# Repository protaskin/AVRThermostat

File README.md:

# AVRThermostat

AVRThermostat is, as the name implies, a programmable thermostat, which is built
on

* Atmel AVR ATmega8A microcontroller,

* digital thermometer DS18B20 by Maxim Integrated,

* four-digit seven-segment led display with common cathode (like CC56-12 or
FYQ-5641A),

and uses a relay to control a heater or fan. The device can be used as a simple
thermometer as well. The sensor measures temperatures from -55°C to +125°C
with ±0.5°C accuracy from -10°C to +85°C.

The thermostat has 4 buttons (Plus, Minus, Set, Reset) that are used to set up
parameters--the setpoint and the zone (delta). The longer you hold the 
Plus/Minus button, the faster a parameter increases/decreases. The Reset button
is used to set the standard value to a parameter, also to switch off the
thermostat mode. Parameters are saved in EEPROM after editing.

The Plus/Minus buttons also are used to adjust the display brightness when
the device is not in the mode of editing of a parameter.

Two leds indicate the state of the relay. If the device is not in the thermostat
mode, then both leds do not light.

If the device cannot establish connection with the sensor, the display shows
an error.

## Schematics and PCB Layout r3.x

A KiCad project, which includes a schematics and PCB layout, is located in
[the Design directory](Design/). **Please be aware that the project is made from
scratch and I have not yet used the new PCB layout myself, therefore it may have
errors.**

### Schematics

### PCB 3D Model

## Versioning

For transparency and insight into our release cycle, and for striving to
maintain backwards compatibility, AVRThermostat will be maintained under the
Semantic Versioning guidelines as much as possible.

For more information on SemVer, please visit http://semver.org/

## License

Copyright 2014-2017 Artyom Protaskin

Licensed under the MIT License:

http://opensource.org/licenses/MIT

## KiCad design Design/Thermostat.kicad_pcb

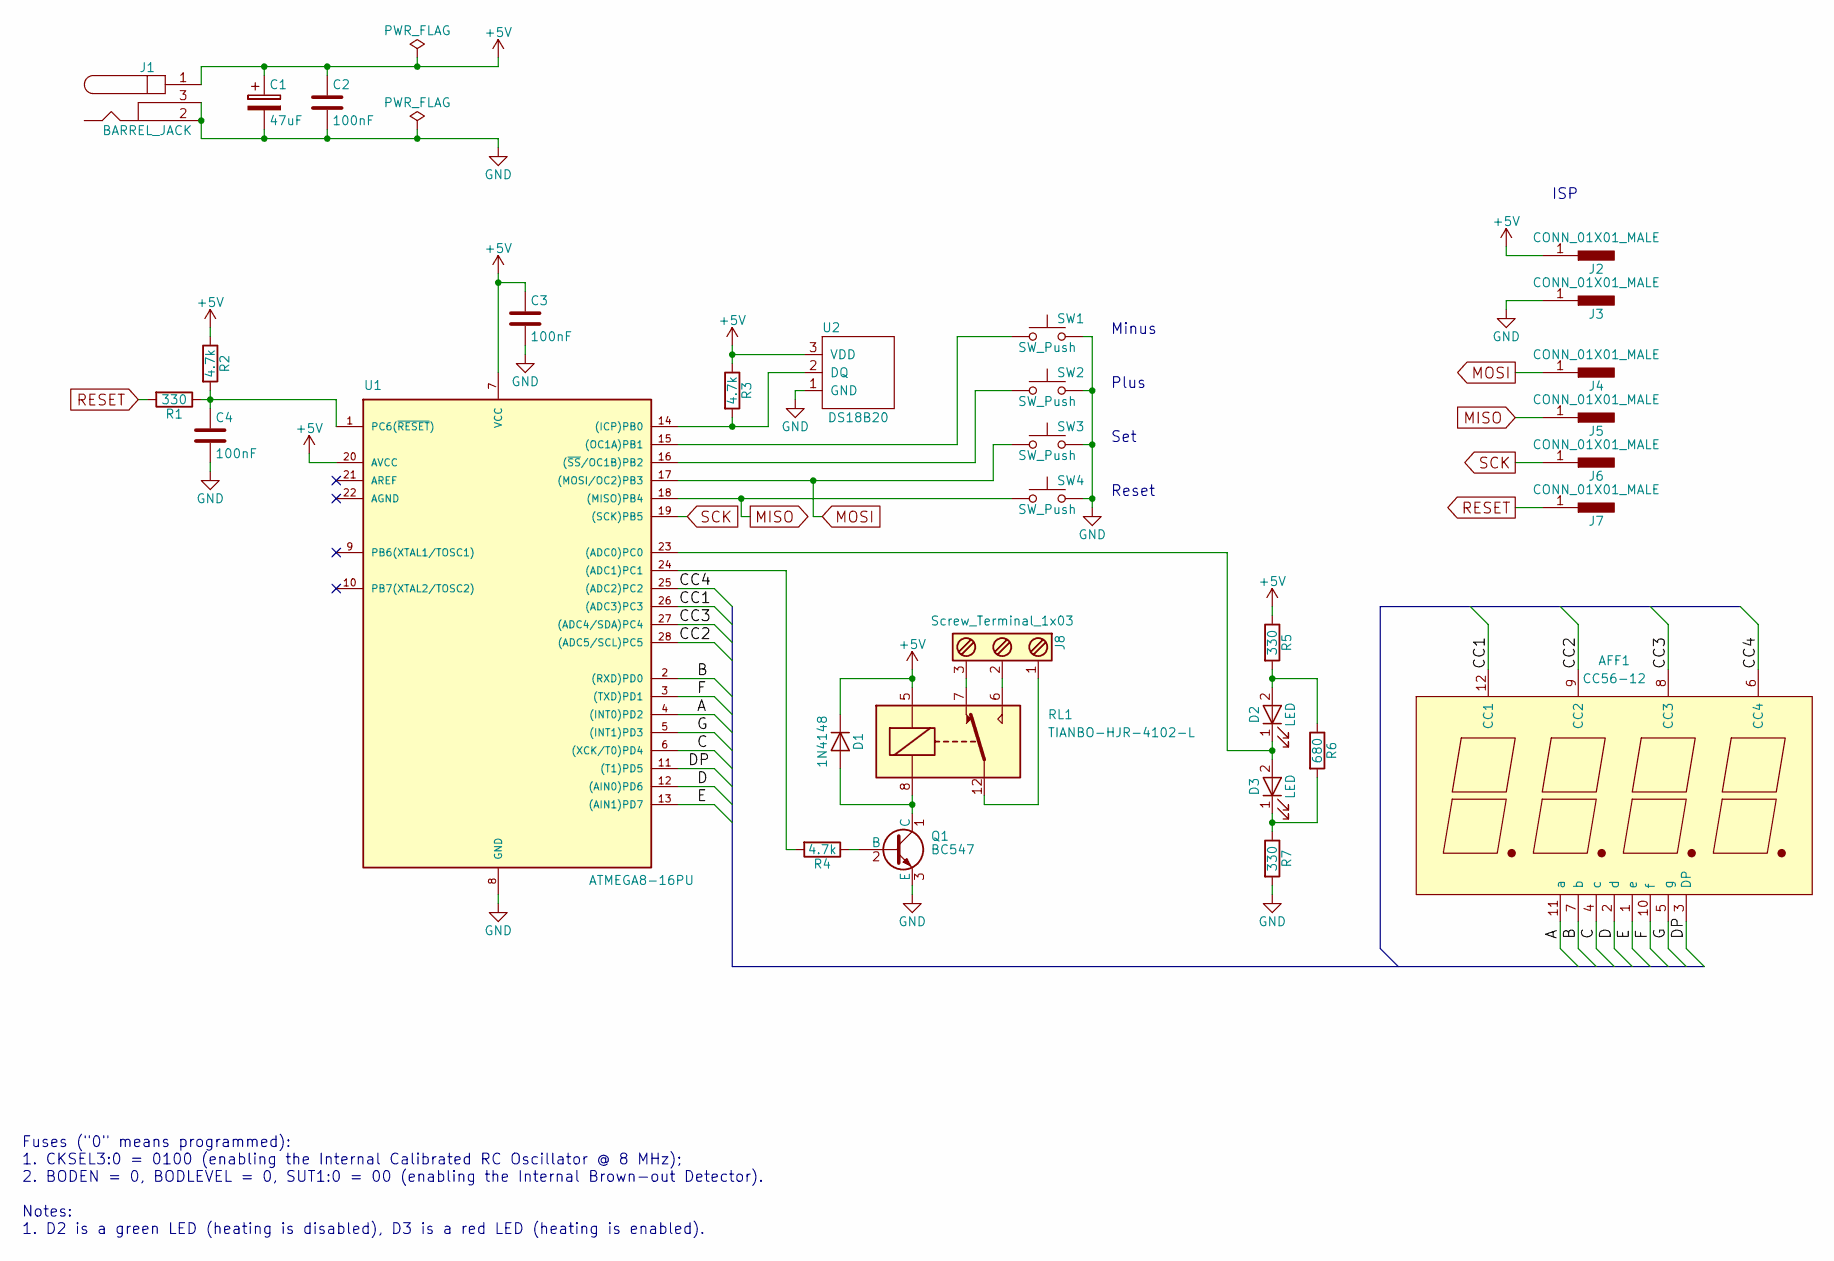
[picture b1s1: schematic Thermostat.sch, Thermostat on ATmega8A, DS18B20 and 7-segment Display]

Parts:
AFF1: CC56-12; CC56-12GWA
C1: 47uF; CP_Radial_D5.0mm_P2.00mm
C2, C3, C4: 100nF; C_Disc_D4.3mm_W1.9mm_P5.00mm
D1: 1N4148; D_DO-35_SOD27_P7.62mm_Horizontal
D2, D3: LED; LED_D3.0mm
J1: BARREL_JACK
J2, J3, J4, J5, J6, J7: CONN_01X01_MALE; Pin_Header_Straight_1x01_Pitch2.54mm
J8: Screw_Terminal_1x03; TerminalBlock_Pheonix_MKDS1.5-3pol
Q1: BC547; TO-92_Molded_Narrow
R1, R5, R7: 330; R_Axial_DIN0207_L6.3mm_D2.5mm_P10.16mm_Horizontal
R2, R3, R4: 4.7k; R_Axial_DIN0207_L6.3mm_D2.5mm_P10.16mm_Horizontal
R6: 680; R_Axial_DIN0207_L6.3mm_D2.5mm_P10.16mm_Horizontal
RL1: TIANBO-HJR-4102-L; Relay_SPDT_HJR-4102
SW1, SW2, SW3, SW4: SW_Push; SW_PUSH_6mm_h5mm
U1: ATMEGA8-16PU; DIP-28_W7.62mm
U2: DS18B20; TO-92_Molded_Narrow

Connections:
+5V: C1.1, C2.1, C3.1, D1.1 (K), J1.1, J2.1, R2.1, R3.1, R5.1, RL1.5, U1.7 (VCC), U1.20 (AVCC), U2.3 (VDD)
/A: AFF1.11 (a), U1.4 ((INT0)PD2)
/B: AFF1.7 (b), U1.2 ((RXD)PD0)
/C: AFF1.4 (c), U1.6 ((XCK/T0)PD4)
/CC1: AFF1.12 (CC1), U1.26 ((ADC3)PC3)
/CC2: AFF1.9 (CC2), U1.28 ((ADC5/SCL)PC5)
/CC3: AFF1.8 (CC3), U1.27 ((ADC4/SDA)PC4)
/CC4: AFF1.6 (CC4), U1.25 ((ADC2)PC2)
/D: AFF1.2 (d), U1.12 ((AIN0)PD6)
/DP: AFF1.3 (DP), U1.11 ((T1)PD5)
/E: AFF1.1 (e), U1.13 ((AIN1)PD7)
/F: AFF1.10 (f), U1.3 ((TXD)PD1)
/G: AFF1.5 (g), U1.5 ((INT1)PD3)
GND: C1.2, C2.2, C3.2, C4.2, J1.2, J1.3, J3.1, Q1.3 (E), R7.2, SW1.2, SW2.2, SW3.2, SW4.2, U1.8 (GND), U2.1 (GND)
MISO: J5.1, SW4.1, U1.18 ((MISO)PB4)
MOSI: J4.1, SW3.1, U1.17 ((MOSI/OC2)PB3)
unnamed: C4.1, R1.1, R2.2, U1.1 (PC6(~RESET~))
unnamed: D1.2 (A), Q1.1 (C), RL1.8
unnamed: D2.1 (K), D3.2 (A), U1.23 ((ADC0)PC0)
unnamed: D2.2 (A), R5.2, R6.1
unnamed: D3.1 (K), R6.2, R7.1
unnamed: J8.1, RL1.12
unnamed: J8.2, RL1.6
unnamed: J8.3, RL1.7
unnamed: Q1.2 (B), R4.1
unnamed: R3.2, U1.14 ((ICP)PB0), U2.2 (DQ)
unnamed: R4.2, U1.24 ((ADC1)PC1)
unnamed: SW1.1, U1.15 ((OC1A)PB1)
unnamed: SW2.1, U1.16 ((~SS~/OC1B)PB2)
RESET: J7.1, R1.2
SCK: J6.1, U1.19 ((SCK)PB5)

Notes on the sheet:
Minus
Plus
Set
Reset
ISP
Fuses ("0" means programmed): 1. CKSEL3:0 = 0100 (enabling the Internal Calibrated RC Oscillator @ 8 MHz); 2. BODEN = 0, BODLEVEL = 0, SUT1:0 = 00 (enabling the Internal Brown-out Detector). Notes: 1. D2 is a green LED (heating is disabled), D3 is a red LED (heating is enabled).

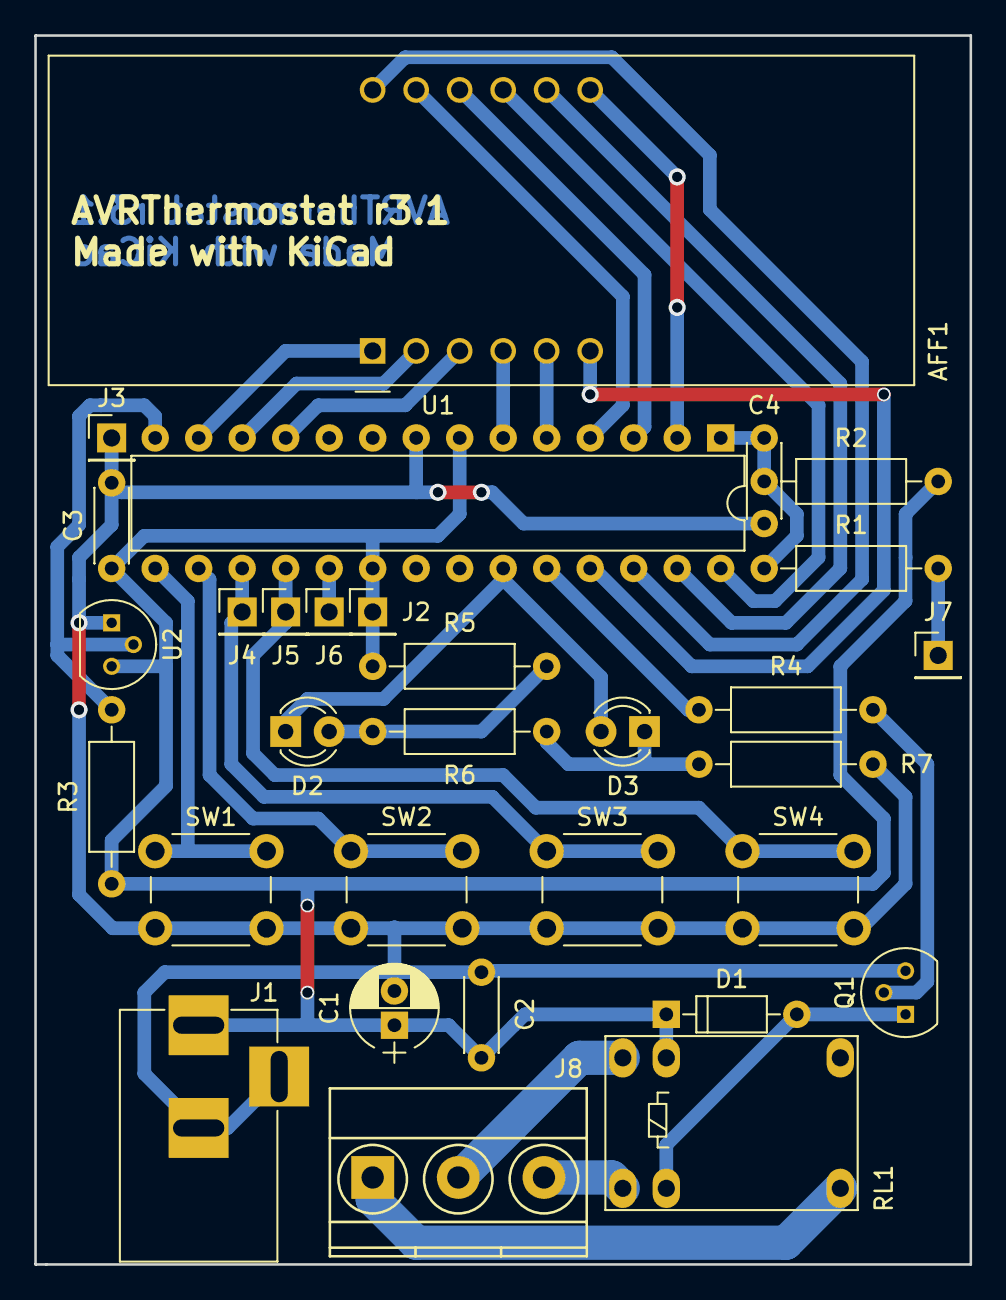
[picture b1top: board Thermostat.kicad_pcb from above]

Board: 2 copper layers, 54.6 x 71.8 mm, 31 parts (0 on the bottom side), 31 nets.

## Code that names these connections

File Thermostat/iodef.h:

/*
 * This file is part of AVRThermostat.
 *
 * (c) Artyom Protaskin <a.protaskin@gmail.com>
 *
 * For the full copyright and license information, please view the LICENSE
 * file that was distributed with this source code.
 */

#ifndef IODEF_H
#define IODEF_H

// Buttons
#define BUTTONS_DDR      DDRB
#define BUTTONS_PORT     PORTB
#define BUTTONS_PIN      PINB
#define MINUS_BUTTON_BIT PB1
#define PLUS_BUTTON_BIT  PB2
#define SET_BUTTON_BIT   PB3
#define RESET_BUTTON_BIT PB4

// LED
#define LED_DDR  DDRC
#define LED_PORT PORTC
#define LED_PIN  PINC
#define LED_BIT  PC0

// Relay
#define RELAY_DDR  DDRC
#define RELAY_PORT PORTC
#define RELAY_PIN  PINC
#define RELAY_BIT  PC1


// Display digits
#define DISPLAY_DIGITS_DDR  DDRC
#define DISPLAY_DIGITS_PORT PORTC
#define DISPLAY_DIGITS_PIN  PINC

#define DISPLAY_1_BIT PC3
#define DISPLAY_2_BIT PC5
#define DISPLAY_3_BIT PC4
#define DISPLAY_4_BIT PC2

// Display segments
#define DISPLAY_SEGMENTS_DDR  DDRD
#define DISPLAY_SEGMENTS_PORT PORTD
#define DISPLAY_SEGMENTS_PIN  PIND

#define DISPLAY_A_BIT  PD2
#define DISPLAY_B_BIT  PD0
#define DISPLAY_C_BIT  PD4
#define DISPLAY_D_BIT  PD6
#define DISPLAY_E_BIT  PD7
#define DISPLAY_F_BIT  PD1
#define DISPLAY_G_BIT  PD3
#define DISPLAY_DP_BIT PD5

// DS18B20
#define DS18B20_DDR  DDRB
#define DS18B20_PORT PORTB
#define DS18B20_PIN  PINB
#define DS18B20_BIT  PB0

#endif /* IODEF_H */

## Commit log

2016-07-17 Use aliases instead of direct usage of i/o registers
2016-11-08 Improve contact debouncing algorithm
2016-11-09 Fix possible reactivation of the leds and relay
    Fix possible reactivation of the leds and relay during switching off
    the thermostat mode by the TIMER1_COMPA_vect interrupt (or by holding
    the reset button pressed (ab3618b regression)).
2016-11-12 Polish the code
2016-12-01 Add macros for the default and limit values of the parameters
2017-01-03 Update the year
2017-01-03 Update the location of the schematics file
2017-01-03 Update the schematics, add the link to the PCB layout in Gerber
2017-01-03 Update the links to the MIT license
2017-07-30 Move the Atmel Studio project files to the their own directory
2017-07-30 Add a design project remade with KiCad
    The new design also includes the following minor changes:
    - Added decoupling capacitors
    - Added "the reset circuit"
    - Connected AVCC to VCC
    - Removed the ISP IDC, added pin headers instead
    - Swapped PC4 and PC5 outputs
2017-07-30 Improve the README files
2017-08-27 Make the calc_pressed_button_delay function private
2017-09-23 Improve use of const parameters and variables
2017-09-23 Rename the mask parameter
    The functions work with bit offsets not masks
2017-09-23 Start using the _BV() macro
2017-09-23 Remove unnecessary use of 16-bit size_t
2017-09-23 Start using the standard boolean type and values
2017-09-23 Add missing includes into the header files
2017-09-23 Refactor the project's macros
    - Replaced the display I/O configuration mask macros with bit offset macros
    - Moved all the I/O configuration macros to iodef.h
    - Renamed DISPLAY_DIGITS_COUNT to DISPLAY_REGISTER_SIZE
2017-09-23 Refactor fill_display_register local variables
2017-09-24 Make the main.c functions private
2017-09-25 Refactor timer1 status byte
2017-09-25 Refactor skipping the power-on reset value of the temperature
2017-09-25 Update the EEPROM-specific code
    - Moved the EEPROM-specific code to the config module
    - Added function to calculate the checksum of the parameters stored
    in EEPROM (uses the standard avr-gcc _crc_ibutton_update function)
    - Added functions to read and update the parameters stored in EEPROM,
    which also check the checksum and keep it updated
    - Added showing an error message in case of reading an incorrect value
2017-09-25 Make the main.c variables private
2017-10-07 Add a recommendation to enabling the BOD
